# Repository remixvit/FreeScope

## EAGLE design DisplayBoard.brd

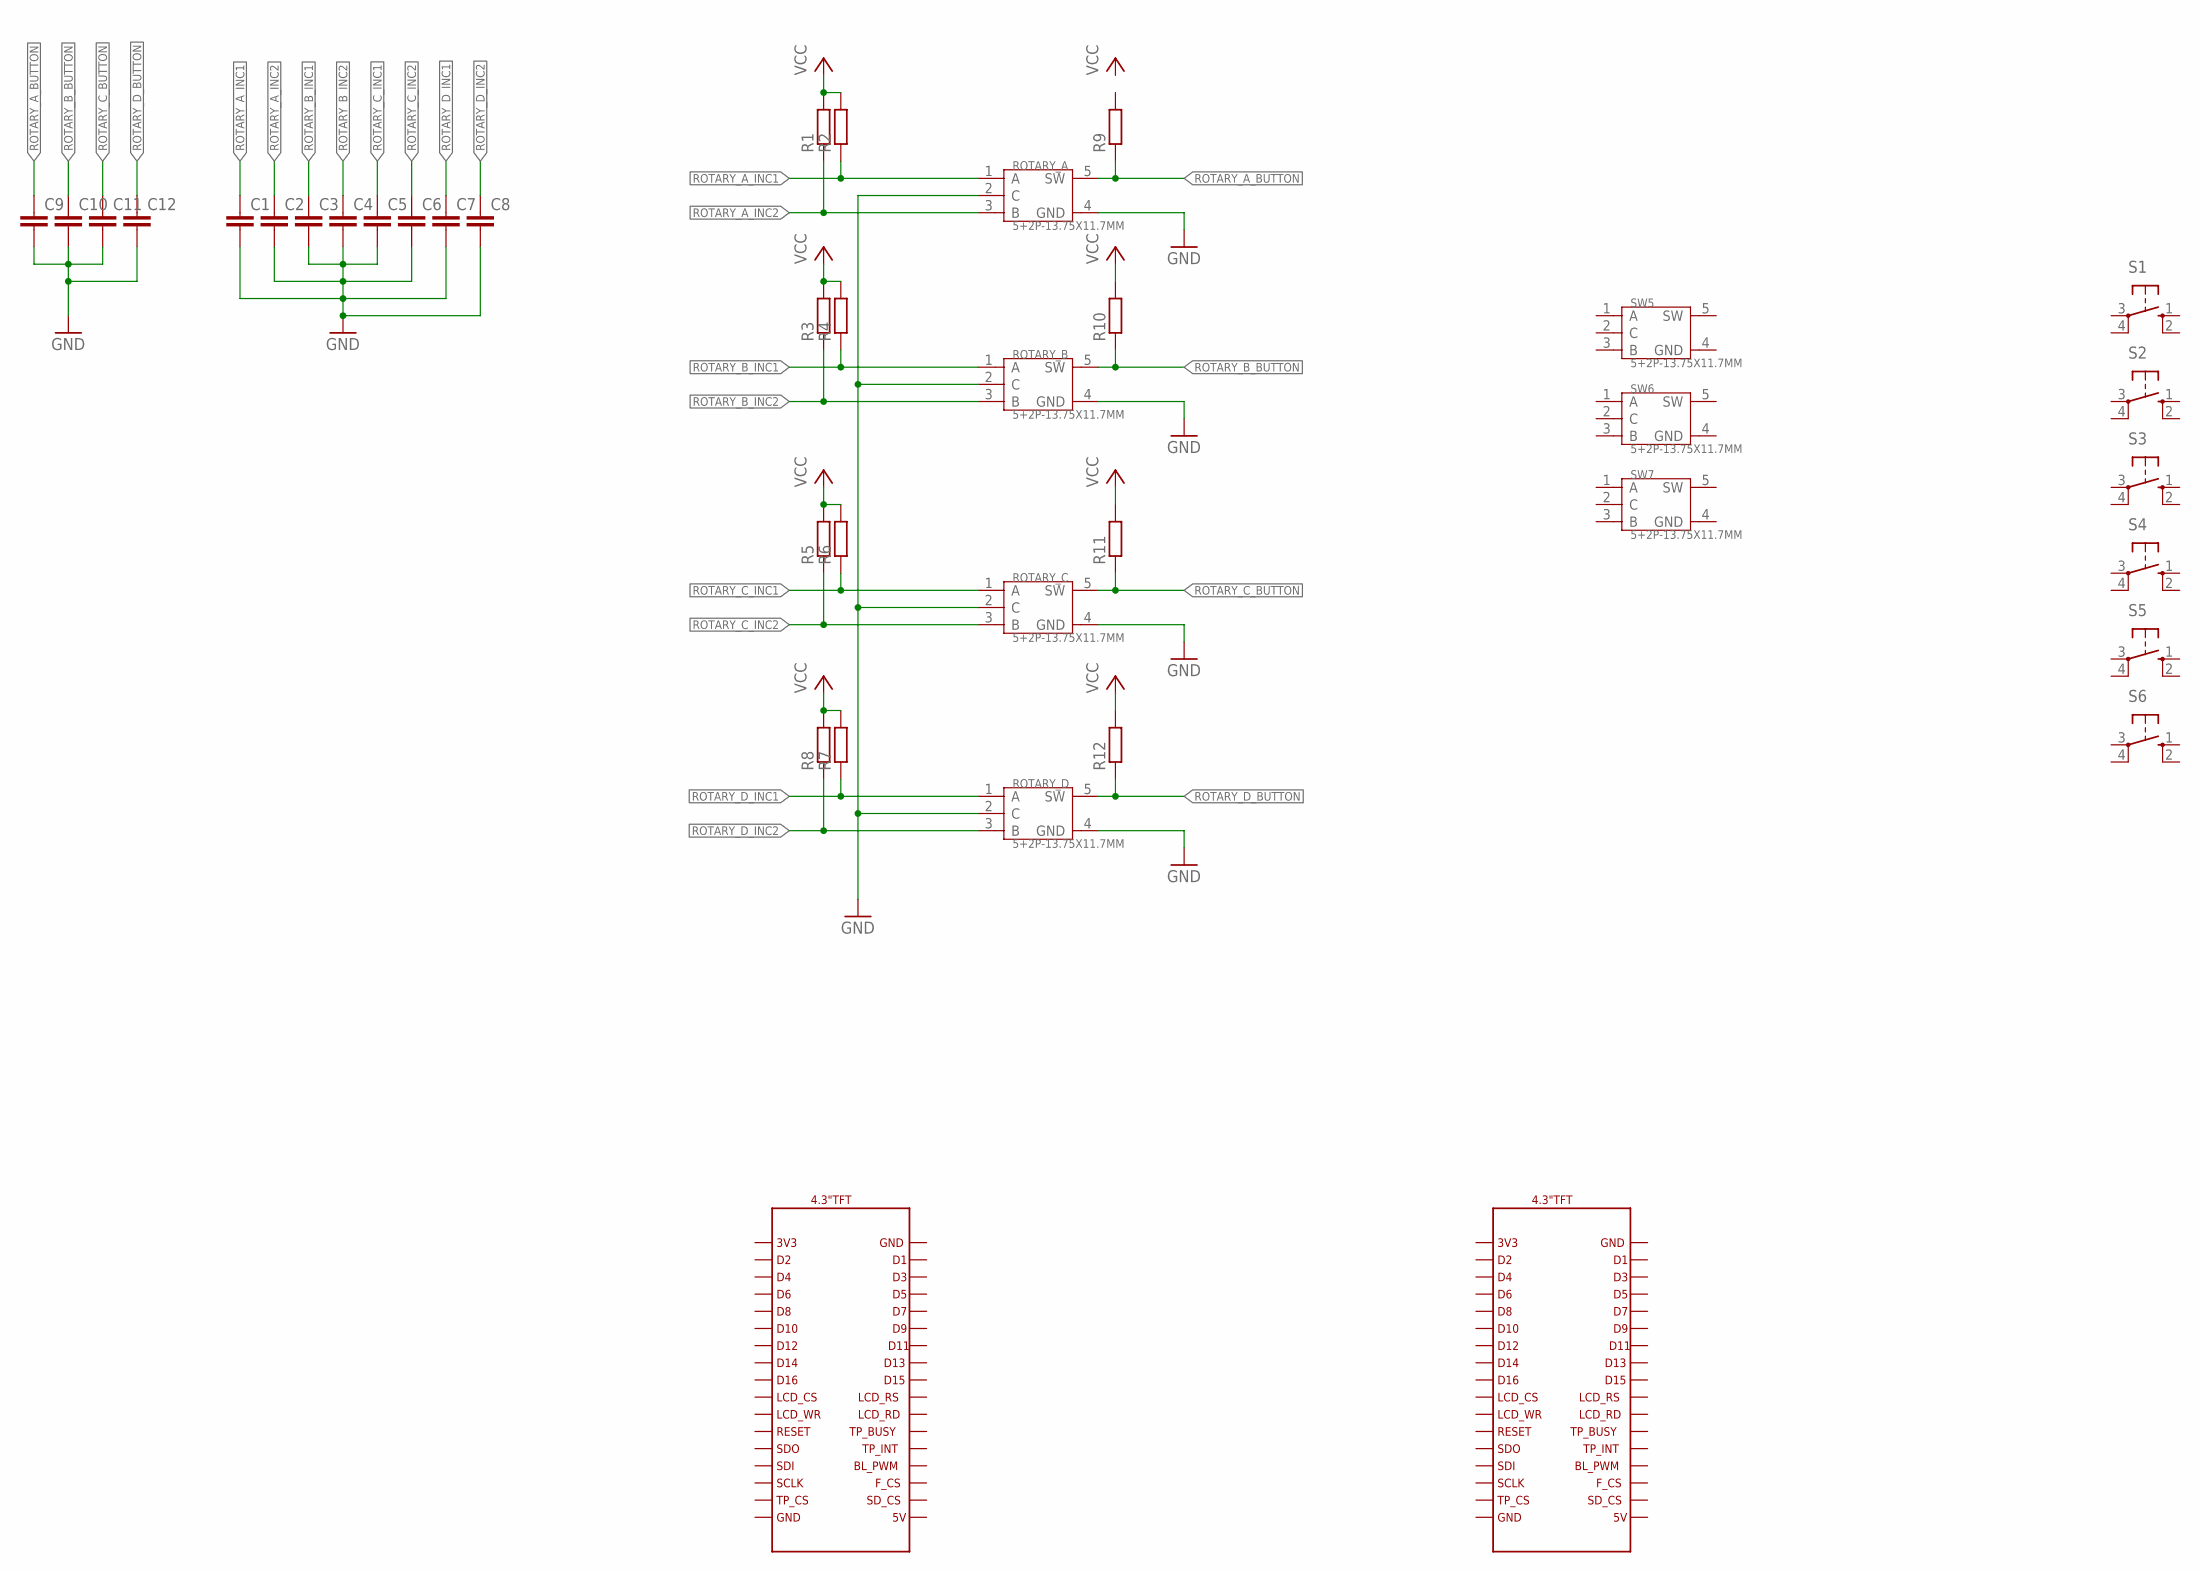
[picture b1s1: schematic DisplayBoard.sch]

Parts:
C1, C2, C3, C4, C5, C6, C7, C8, C9, C10, C11, C12: C-EUC0805; C0805
R1, R2, R3, R4, R5, R6, R7, R8, R9, R10, R11, R12: R-EU_R0805; R0805
ROTARY_A: 5+2P-13.75X11.7MM; SW7-13.75X11.7X6.5MM
ROTARY_B: 5+2P-13.75X11.7MM; SW7-13.75X11.7X6.5MM
ROTARY_C: 5+2P-13.75X11.7MM; SW7-13.75X11.7X6.5MM
ROTARY_D: 5+2P-13.75X11.7MM; SW7-13.75X11.7X6.5MM
S1, S2, S3, S4, S5, S6: 10-XX; B3F-10XX
SW5, SW6, SW7: 5+2P-13.75X11.7MM; SW7-13.75X11.7X6.5MM
U$1: 4.3"TFT; 4.3TFT

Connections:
GND: C1.2, C2.2, C3.2, C4.2, C5.2, C6.2, C7.2, C8.2, C9.2, C10.2, C11.2, C12.2, ROTARY_A.2 (C), ROTARY_A.4 (GND), ROTARY_B.2 (C), ROTARY_B.4 (GND), ROTARY_C.2 (C), ROTARY_C.4 (GND), ROTARY_D.2 (C), ROTARY_D.4 (GND)
ROTARY_A_BUTTON: C9.1, R9.1, ROTARY_A.5 (SW)
ROTARY_A_INC1: C1.1, R2.1, ROTARY_A.1 (A)
ROTARY_A_INC2: C2.1, R1.1, ROTARY_A.3 (B)
ROTARY_B_BUTTON: C10.1, R10.1, ROTARY_B.5 (SW)
ROTARY_B_INC1: C3.1, R4.1, ROTARY_B.1 (A)
ROTARY_B_INC2: C4.1, R3.1, ROTARY_B.3 (B)
ROTARY_C_BUTTON: C11.1, R11.1, ROTARY_C.5 (SW)
ROTARY_C_INC1: C5.1, R6.1, ROTARY_C.1 (A)
ROTARY_C_INC2: C6.1, R5.1, ROTARY_C.3 (B)
ROTARY_D_BUTTON: C12.1, R12.1, ROTARY_D.5 (SW)
ROTARY_D_INC1: C7.1, R7.1, ROTARY_D.1 (A)
ROTARY_D_INC2: C8.1, R8.1, ROTARY_D.3 (B)
VCC: R1.2, R2.2, R3.2, R4.2, R5.2, R6.2, R7.2, R8.2, R10.2, R11.2, R12.2

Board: 2 copper layers, 38 parts (0 on the bottom side), 14 nets, no tracks yet.

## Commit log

2016-03-29 Create LCD board and Layout
